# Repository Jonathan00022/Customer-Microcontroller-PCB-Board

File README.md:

# Customer Microcontroller PCB Board Template

Welcome! This repository provides a **custom microcontroller board template** designed for IoT and embedded systems hobbyists. It’s both a learning tool and a starting point for custom projects. **Anyone can add their own ideas, modifications, or features here**: just fork, edit, and contribute!

## What’s Inside

- **KiCad Project Files**: Full schematics and PCB layout editable in KiCad.
- **Sample BOM**: Example bill of materials in CSV format.
- **3D Board View**: Visual PNG previews of the assembled board.
- **Schematics Image**: Quick reference schematic as PNG.
- **Open License**: All files licensed with Unlicense for free reuse.

## Who Is This For?

- Hobbyists exploring PCB design or IoT prototyping
- Students and educators needing a microcontroller board template for embedded projects
- Makers customizing boards for their needs (add, modify, remix as you like!)

## How to Use

1. **Clone or Download** the repository.
2. **Open the KiCad project** files (.kicad_pro, .kicad_sch, .kicad_pcb, etc.).
3. **Edit**: Add your own components, change the schematic, or modify the PCB layout.
4. **View**: Use the `Schematics image.png` and `3D View.png` for reference.
5. **Contribute**: Share your improvements or new features by making a pull request.

## Directory Structure

- `Customer MicroController Board.kicad_pro`
- `Customer MicroController Board.kicad_sch`
- `Customer MicroController Board.kicad_pcb`
- `Customer MicroController Board.csv` — Bill of Materials
- `Schematics image.png` — Schematic reference
- `3D View.png` — Board visualization
- `LICENSE` — Unlicense for maximum freedom

## How to Contribute

- Fork the repository
- Add your changes (new components, features, fixes)
- Submit a pull request describing what’s new
- **Every suggestion and addition is welcome!**

## Credits

- Built by and for hobbyists, makers, and learners.
- Major contributor: MuhireJonathan (https://github.com/Jonathan00022)

**Feel free to personalize or extend this template as needed!**

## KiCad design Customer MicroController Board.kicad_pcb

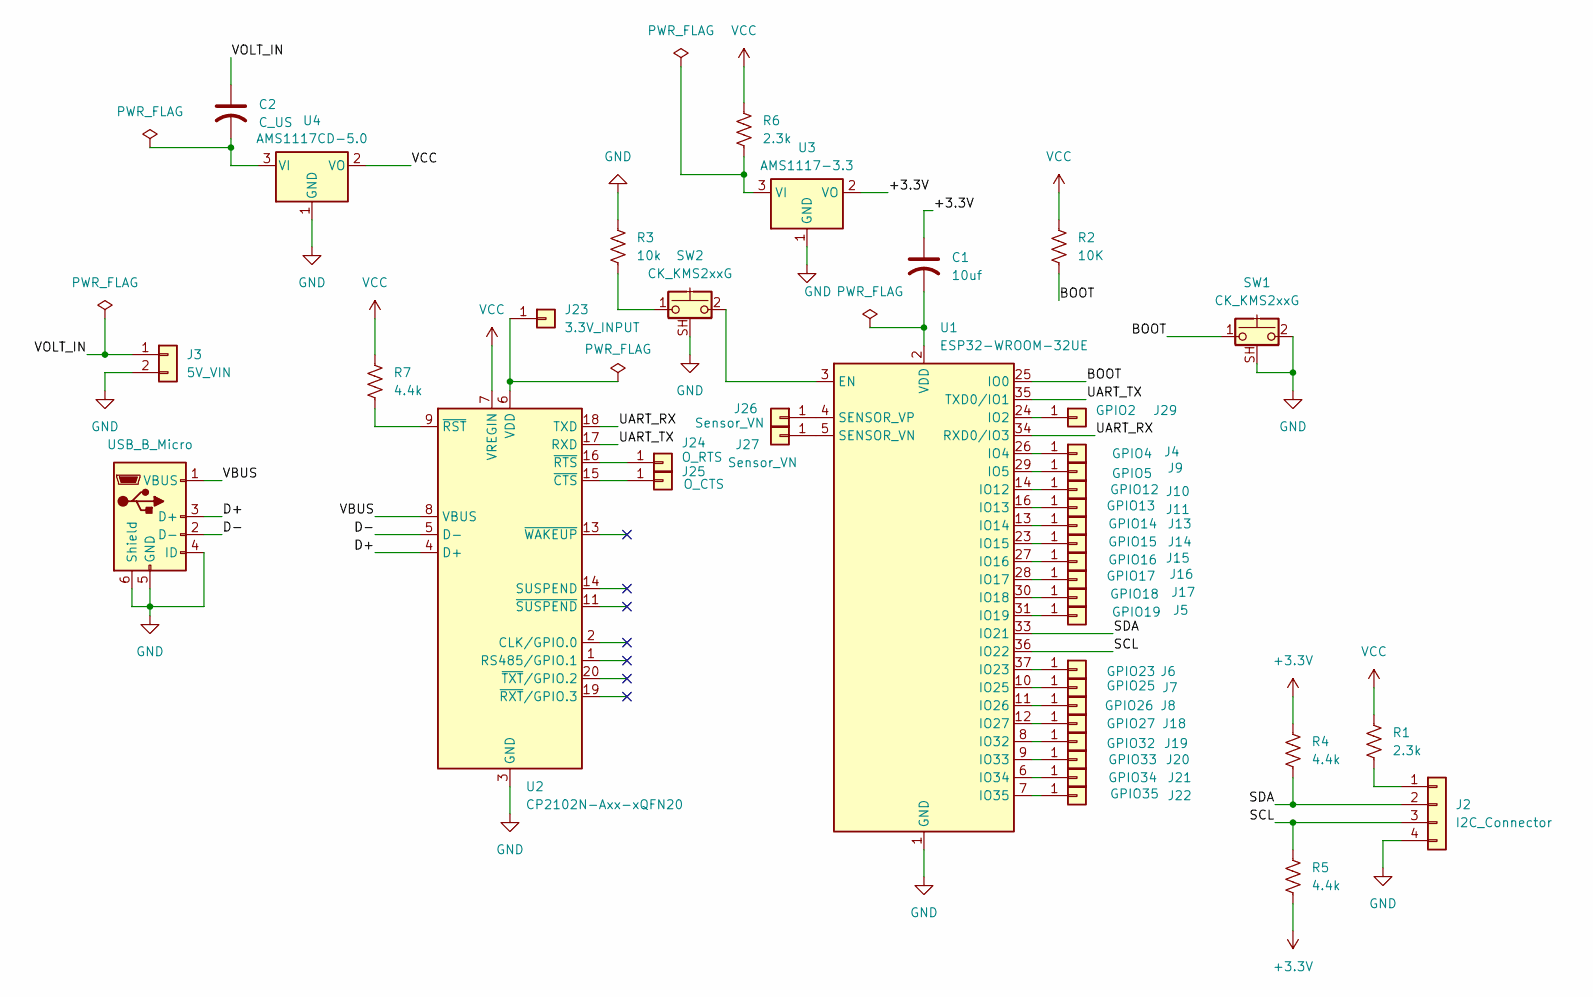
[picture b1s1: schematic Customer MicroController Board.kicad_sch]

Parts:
C1: 10uf; CP_EIA-1608-08_AVX-J_HandSolder
C2: C_US; C_0201_0603Metric_Pad0.64x0.40mm_HandSolder
J1: USB_B_Micro; USB_Micro-AB_Molex_47590-0001
J2: I2C_Connector; Hirose_DF3EA-04P-2H_1x04-1MP_P2.00mm_Horizontal
J3: 5V_VIN; Hirose_DF3EA-02P-2H_1x02-1MP_P2.00mm_Horizontal
J4: GPIO4; Hirose_DF63M-1P-3.96DSA_1x01_P3.96mm_Vertical
J5: GPIO19; Hirose_DF63M-1P-3.96DSA_1x01_P3.96mm_Vertical
J6: GPIO23; Hirose_DF63M-1P-3.96DSA_1x01_P3.96mm_Vertical
J7: GPIO25; Hirose_DF63M-1P-3.96DSA_1x01_P3.96mm_Vertical
J8: GPIO26; Hirose_DF63M-1P-3.96DSA_1x01_P3.96mm_Vertical
J9: GPIO5; Hirose_DF63M-1P-3.96DSA_1x01_P3.96mm_Vertical
J10: GPIO12; Hirose_DF63M-1P-3.96DSA_1x01_P3.96mm_Vertical
J11: GPIO13; Hirose_DF63M-1P-3.96DSA_1x01_P3.96mm_Vertical
J13: GPIO14; Hirose_DF63M-1P-3.96DSA_1x01_P3.96mm_Vertical
J14: GPIO15; Hirose_DF63M-1P-3.96DSA_1x01_P3.96mm_Vertical
J15: GPIO16; Hirose_DF63M-1P-3.96DSA_1x01_P3.96mm_Vertical
J16: GPIO17; Hirose_DF63M-1P-3.96DSA_1x01_P3.96mm_Vertical
J17: GPIO18; Hirose_DF63M-1P-3.96DSA_1x01_P3.96mm_Vertical
J18: GPIO27; Hirose_DF63M-1P-3.96DSA_1x01_P3.96mm_Vertical
J19: GPIO32; Hirose_DF63M-1P-3.96DSA_1x01_P3.96mm_Vertical
J20: GPIO33; Hirose_DF63M-1P-3.96DSA_1x01_P3.96mm_Vertical
J21: GPIO34; Hirose_DF63M-1P-3.96DSA_1x01_P3.96mm_Vertical
J22: GPIO35; Hirose_DF63M-1P-3.96DSA_1x01_P3.96mm_Vertical
J23: 3.3V_INPUT; PinSocket_1x01_P2.00mm_Vertical
J24: O_RTS; PinSocket_1x01_P2.00mm_Vertical
J25: O_CTS; PinSocket_1x01_P2.00mm_Vertical
J26, J27: Sensor_VN; PinSocket_1x01_P2.00mm_Vertical
J29: GPIO2; Hirose_DF63M-1P-3.96DSA_1x01_P3.96mm_Vertical
R1, R6: 2.3k; R_0201_0603Metric
R2: 10K; R_0201_0603Metric
R3: 10k; R_0201_0603Metric
R4, R5, R7: 4.4k; R_0201_0603Metric
SW1, SW2: CK_KMS2xxG; SW_SPST_CK_KMS2xxGP
U1: ESP32-WROOM-32UE
U2: CP2102N-Axx-xQFN20; SiliconLabs_QFN-20-1EP_3x3mm_P0.5mm_EP1.8x1.8mm
U3: AMS1117-3.3; SOT-223-3_TabPin2
U4: AMS1117CD-5.0; TO-252-3_TabPin2

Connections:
+3.3V: C1.1, R4.1, R5.2, U3.2 (VO)
/BOOT: R2.2, SW1.1, U1.25 (IO0)
/D+: J1.3 (D+), U2.4 (D+)
/D-: J1.2 (D-), U2.5 (D-)
/SCL: J2.3, R5.1, U1.36 (IO22)
/SDA: J2.2, R4.2, U1.33 (IO21)
/UART_RX: U1.34 (RXD0/IO3), U2.18 (TXD)
/UART_TX: U1.35 (TXD0/IO1), U2.17 (RXD)
/VBUS: J1.1 (VBUS), U2.8 (VBUS)
/VOLT_IN: C2.1, J3.1
GND: J1.4 (ID), J1.5 (GND), J1.6 (Shield), J2.4, J3.2, R3.1, SW1.2, SW1.SH (B), SW2.SH (B), U1.1 (GND), U1.15 (GND), U1.38 (GND), U1.39 (GND), U2.3 (GND), U2.12 (GND), U2.21 (GND), U3.1 (GND), U4.1 (GND)
unnamed: J2.1, R1.2
unnamed: J4.1, U1.26 (IO4)
unnamed: J5.1, U1.31 (IO19)
unnamed: J6.1, U1.37 (IO23)
unnamed: J7.1, U1.10 (IO25)
unnamed: J8.1, U1.11 (IO26)
unnamed: J9.1, U1.29 (IO5)
unnamed: J10.1, U1.14 (IO12)
unnamed: J11.1, U1.16 (IO13)
unnamed: J13.1, U1.13 (IO14)
unnamed: J14.1, U1.23 (IO15)
unnamed: J15.1, U1.27 (IO16)
unnamed: J16.1, U1.28 (IO17)
unnamed: J17.1, U1.30 (IO18)
unnamed: J18.1, U1.12 (IO27)
unnamed: J19.1, U1.8 (IO32)
unnamed: J20.1, U1.9 (IO33)
unnamed: J21.1, U1.6 (IO34)
unnamed: J22.1, U1.7 (IO35)
unnamed: J23.1, U2.6 (VDD)
unnamed: J24.1, U2.16 (~RTS)
unnamed: J25.1, U2.15 (~CTS)
unnamed: J26.1, U1.4 (SENSOR_VP)
unnamed: J27.1, U1.5 (SENSOR_VN)
unnamed: J29.1, U1.24 (IO2)
unnamed: R3.2, SW2.1
unnamed: SW2.2, U1.3 (EN)
unnamed: C1.2, U1.2 (VDD)
unnamed: R7.2, U2.9 (~RST)
unnamed: R6.2, U3.3 (VI)
unnamed: C2.2, U4.3 (VI)
VCC: R1.1, R2.1, R6.1, R7.1, U2.7 (VREGIN), U4.2 (VO)

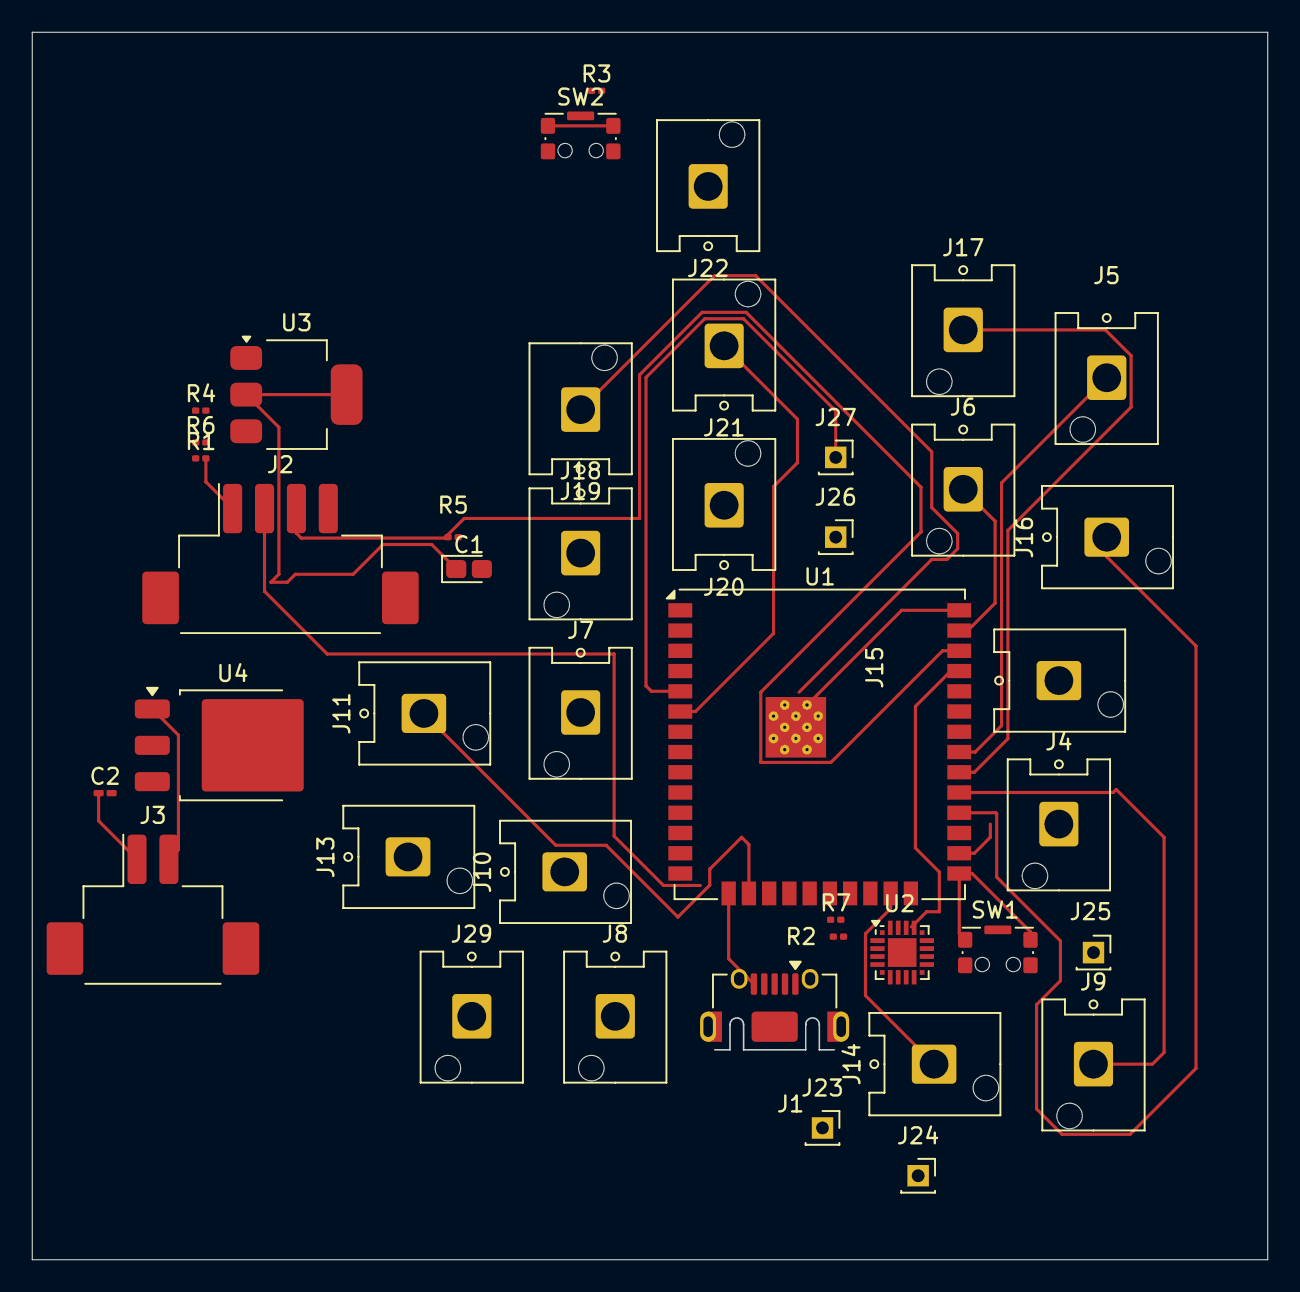
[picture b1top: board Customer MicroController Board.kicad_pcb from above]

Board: 2 copper layers, 77.5 x 77.0 mm, 42 parts (0 on the bottom side), 43 nets.

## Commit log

2025-11-22 feat: Customer microcontroller board template
2025-11-22 Add README
    This README provides an overview of the customer microcontroller PCB board template, including its contents, intended audience, usage instructions, directory structure, contribution guidelines, and c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
